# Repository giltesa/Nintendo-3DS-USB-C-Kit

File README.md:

# Nintendo 3DS USB-C Kit

The **Nintendo 3DS: USB-C Kit** is a board that allows to replace the original charging connector for a modern and standard **USB-C**.

**If your original connector is too old or damaged** and you need a new one, or **if you would like to charge your Nintendo 3DS with a standard USB-C charger**, like the charger of your **Nintendo Switch**, phone, laptop, you can with this kit.

This board is compatible with these four models:

*   Nintendo 3DS
*   Nintendo 3DS XL
*   Nintendo New 3DS
*   Nintendo New 3DS XL

The kit also includes a plastic piece which can holder the dock metal contacts from the original connector, that means you will be able to **charge it by USB-C** but also with the **charging dock**.

## Would you like it?

https://shop.giltesa.com/product/nintendo-3ds-usb-c-kit/

## More

- [giltesa.com](https://giltesa.com "giltesa.com")
- [twitter.com](https://twitter.com/giltesa "twitter.com")

## License

This project is licensed under a **Creative Commons** license:
**[Attribution-NonCommercial-ShareAlike 4.0 International (CC BY-NC-SA 4.0) ](https://creativecommons.org/licenses/by-nc-sa/4.0/)**

Check the [LICENSE.md](LICENSE.md) for more information.

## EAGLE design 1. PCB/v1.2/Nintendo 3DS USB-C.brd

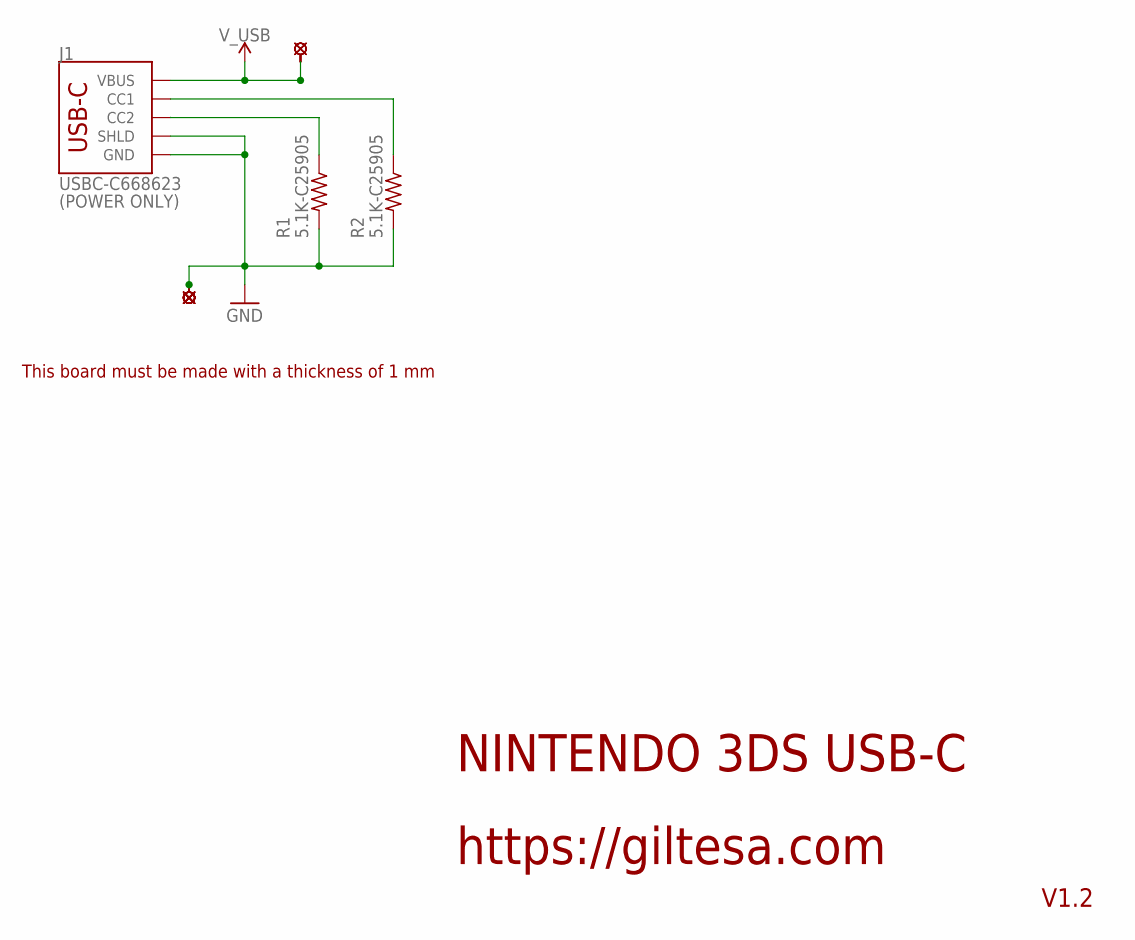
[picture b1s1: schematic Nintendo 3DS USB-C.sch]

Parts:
J1: USBC-C668623; USB-C_6P
R1, R2: 5.1K-C25905; R0402
U$2, U$3, U$4, U$6, U$7, U$8: PAD_1.0H; PAD_1.0_HALF_MASK

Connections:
GND: J1.A12-GND (GND), J1.B12-GND (GND), J1.SHLD1 (SHLD), J1.SHLD2 (SHLD), J1.SHLD3 (SHLD), J1.SHLD4 (SHLD), R1.2, R2.2, U$4.P$1, U$6.P$1, U$7.P$1, U$8.P$1
unnamed: J1.B5 (CC2), R1.1
unnamed: J1.A5 (CC1), R2.1
V_USB: J1.A9-VBUS (VBUS), J1.B9-VBUS (VBUS), U$2.P$1, U$3.P$1

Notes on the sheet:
NINTENDO 3DS USB-C
https://giltesa.com
V1.2
This board must be made with a thickness of 1 mm
(POWER ONLY)

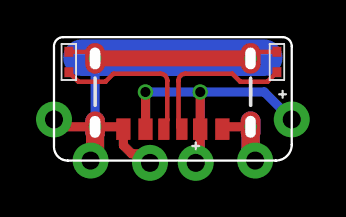
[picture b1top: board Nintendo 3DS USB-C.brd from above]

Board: 2 copper layers, 13.2 x 6.9 mm, 10 parts (1 on the bottom side), 4 nets.

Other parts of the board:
U$11: GILTESA.COM_MASK_7MM

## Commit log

2023-03-24 no message
2023-05-09 v1.0
2023-05-09 v1.1
2023-05-09 test
2024-01-15 v1.2

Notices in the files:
parts and their libraries:
SparkFun: Licensing: CC v3.0 Share-Alike You are welcome to use this library for commercial purposes.
SparkFun-PowerSymbols: Licensing: Creative Commons ShareAlike 4.0 International - https://creativecommons.org/licenses/by-sa/4.0
